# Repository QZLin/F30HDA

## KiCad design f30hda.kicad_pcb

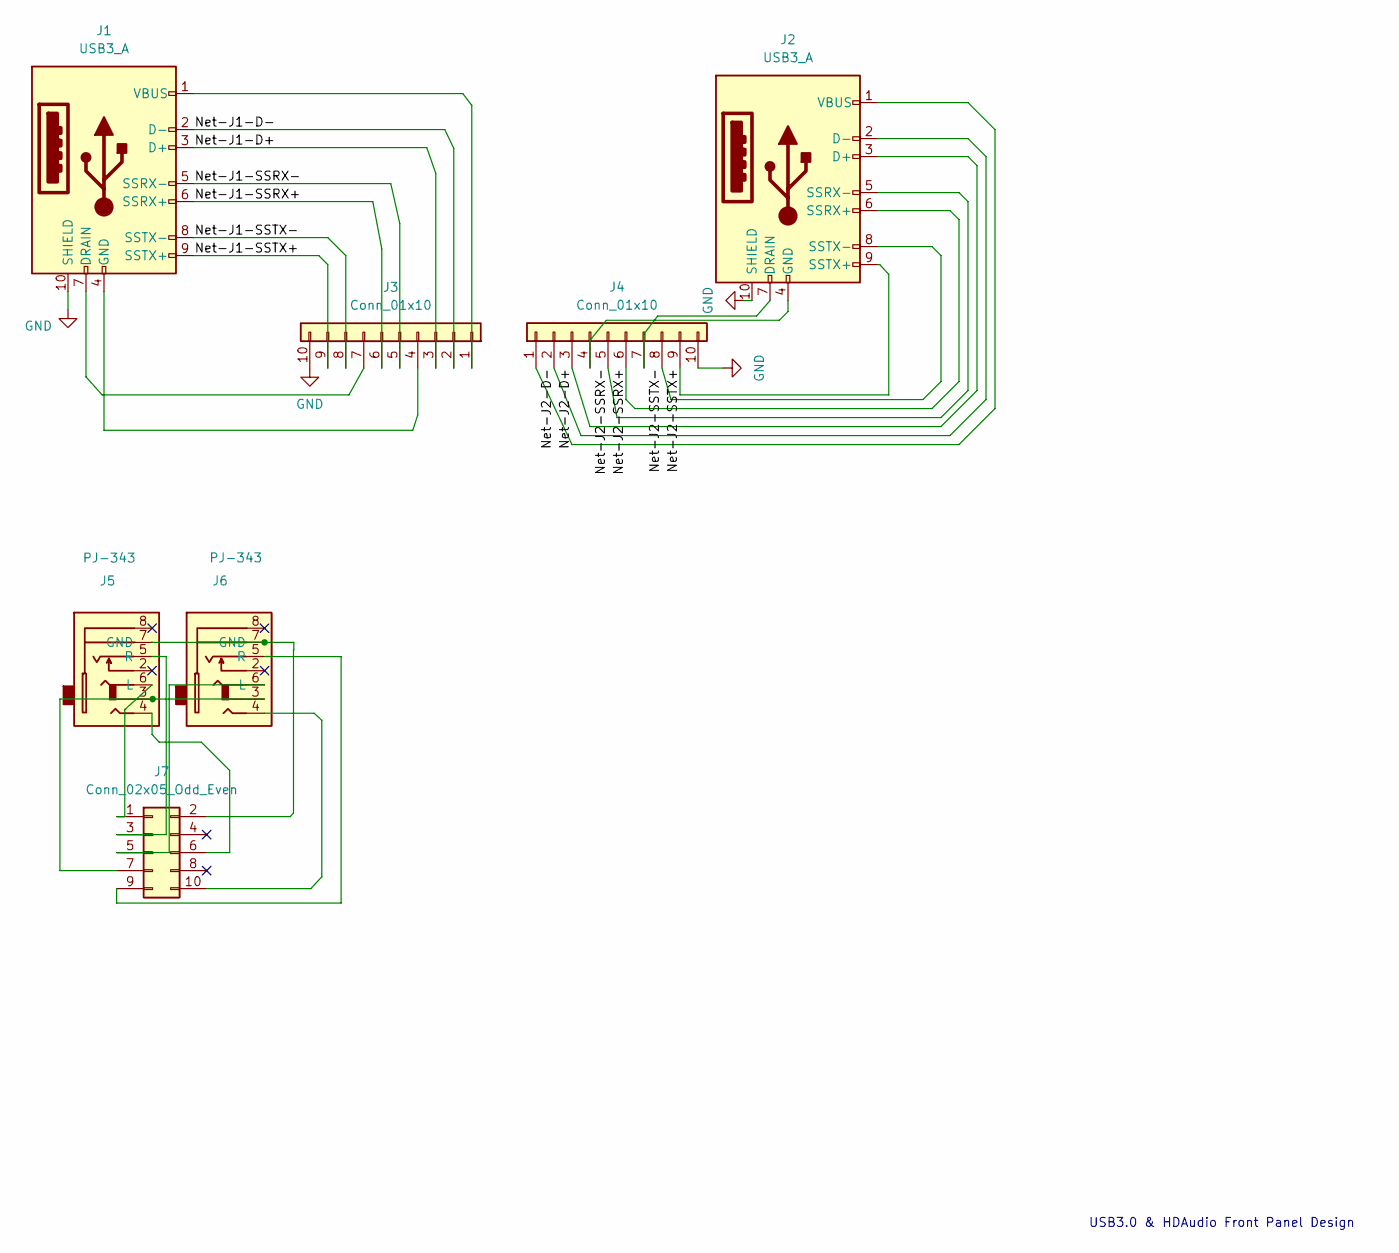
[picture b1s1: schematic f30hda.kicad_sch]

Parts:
J1, J2: USB3_A; USB3_A_Molex_48393-001
J3, J4: Conn_01x10; PinHeader_1x10_P1.00mm_Vertical
J5, J6: PJ-343; AudioJack_3.5mm_PJ-343
J7: Conn_02x05_Odd_Even; PinSocket_2x05_P1.27mm_Vertical

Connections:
/Net-J1-D+: J1.3 (D+), J3.3
/Net-J1-D-: J1.2 (D-), J3.2
/Net-J1-SSRX+: J1.6 (SSRX+), J3.6
/Net-J1-SSRX-: J1.5 (SSRX-), J3.5
/Net-J1-SSTX+: J1.9 (SSTX+), J3.9
/Net-J1-SSTX-: J1.8 (SSTX-), J3.8
/Net-J2-D+: J2.3 (D+), J4.3
/Net-J2-D-: J2.2 (D-), J4.2
/Net-J2-SSRX+: J2.6 (SSRX+), J4.6
/Net-J2-SSRX-: J2.5 (SSRX-), J4.5
/Net-J2-SSTX+: J2.9 (SSTX+), J4.9
/Net-J2-SSTX-: J2.8 (SSTX-), J4.8
GND: J1.10 (SHIELD), J2.10 (SHIELD), J3.10, J4.10
unnamed: J1.7 (DRAIN), J3.7
unnamed: J1.4 (GND), J3.4
unnamed: J1.1 (VBUS), J3.1
unnamed: J2.7 (DRAIN), J4.7
unnamed: J2.4 (GND), J4.4
unnamed: J2.1 (VBUS), J4.1
unnamed: J5.7 (GND), J6.7 (GND), J7.2
unnamed: J5.6 (L), J7.1
unnamed: J5.5 (R), J7.3
unnamed: J6.6 (L), J7.5
unnamed: J6.5 (R), J7.9
unnamed: J5.4, J7.6
unnamed: J5.3, J6.3, J7.7
unnamed: J6.4, J7.10

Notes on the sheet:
USB3.0 & HDAudio Front Panel Design

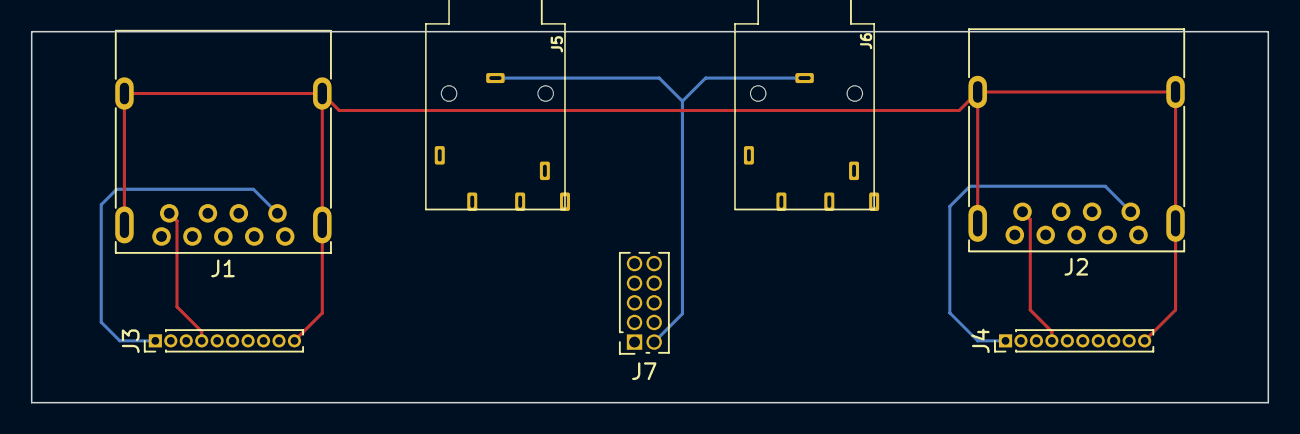
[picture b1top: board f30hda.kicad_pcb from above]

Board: 4 copper layers, 80.0 x 24.0 mm, 7 parts (0 on the bottom side), 27 nets.

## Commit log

2024-02-12 init
2024-02-12 add required logo
